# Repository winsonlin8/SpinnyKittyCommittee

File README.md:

# Spinning Cat Speaker

A rhythm-synchronized speaker system featuring a 3D-printed cat that spins and flashes RGB LEDs in time with music — inspired by [this video](https://www.youtube.com/watch?v=IxX_QHay02M).

**Group Members:** Katherine Han, Evan Ho, Hajime Kioi, Winson Lin

---

## Overview

The Spinning Cat Speaker is a custom-built embedded audio system that plays music while driving a DC motor to spin a 3D-printed cat figurine in sync with the beat. An RGB LED ring mounted on the assembly pulses with the music for a visual effect that complements the audio.

The system is powered via a 5V USB connection and streams audio and motor movement data concurrently from a microSD card. Physical buttons allow the user to cycle through tracks, control playback, and trigger LED effects.

---

## Features

- Music playback from microSD card over I2S to a Class D amplifier
- Motor speed and direction synchronized to music rhythm
- 35-LED WS2812 RGB ring with programmable lighting effects
- Microphone input for audio-reactive modes
- 8-button interface: Play/Pause, Volume Up/Down, Next, Previous, LED Trigger, Microphone Trigger, and a spare
- 5V USB powered

---

## System Architecture

The system is built around two microcontrollers:

- **ESP32** (Main Compute) — handles audio decoding and playback, microSD streaming via SPI, I2S audio output to the amplifier and input from the microphone, button input handling, and I2C communication to the peripheral controller.
- **MSPM0G3507** (Peripheral Control) — receives commands from the ESP32 over I2C and drives the motor via PWM/GPIO to the L298N motor driver, and controls the WS2812 LED ring over a 1-wire interface.

### Component Summary

| Component | Role |
|---|---|
| ESP32 | Main compute: audio, SD, buttons, I2C master |
| MSPM0G3507 | Peripheral control: motor, LEDs (I2C target) |
| ADA254 (microSD Breakout) | Music and movement file storage (SPI) |
| ICS-43434 | MEMS microphone (I2S) |
| MAX98357A | I2S Class D amplifier |
| EK1725 (2"–3", 4Ω, 3W) | Speaker |
| L298N | DC motor driver (PWM + GPIO direction) |
| DC Motor | Spins the cat |
| 35x WS2812 5050 LED Ring | RGB lighting effects (1-wire) |
| 8 Buttons | User input (GPIO with pull-ups) |

### System Diagram

---

## Power

The entire system is powered from a single **5V USB** connection.

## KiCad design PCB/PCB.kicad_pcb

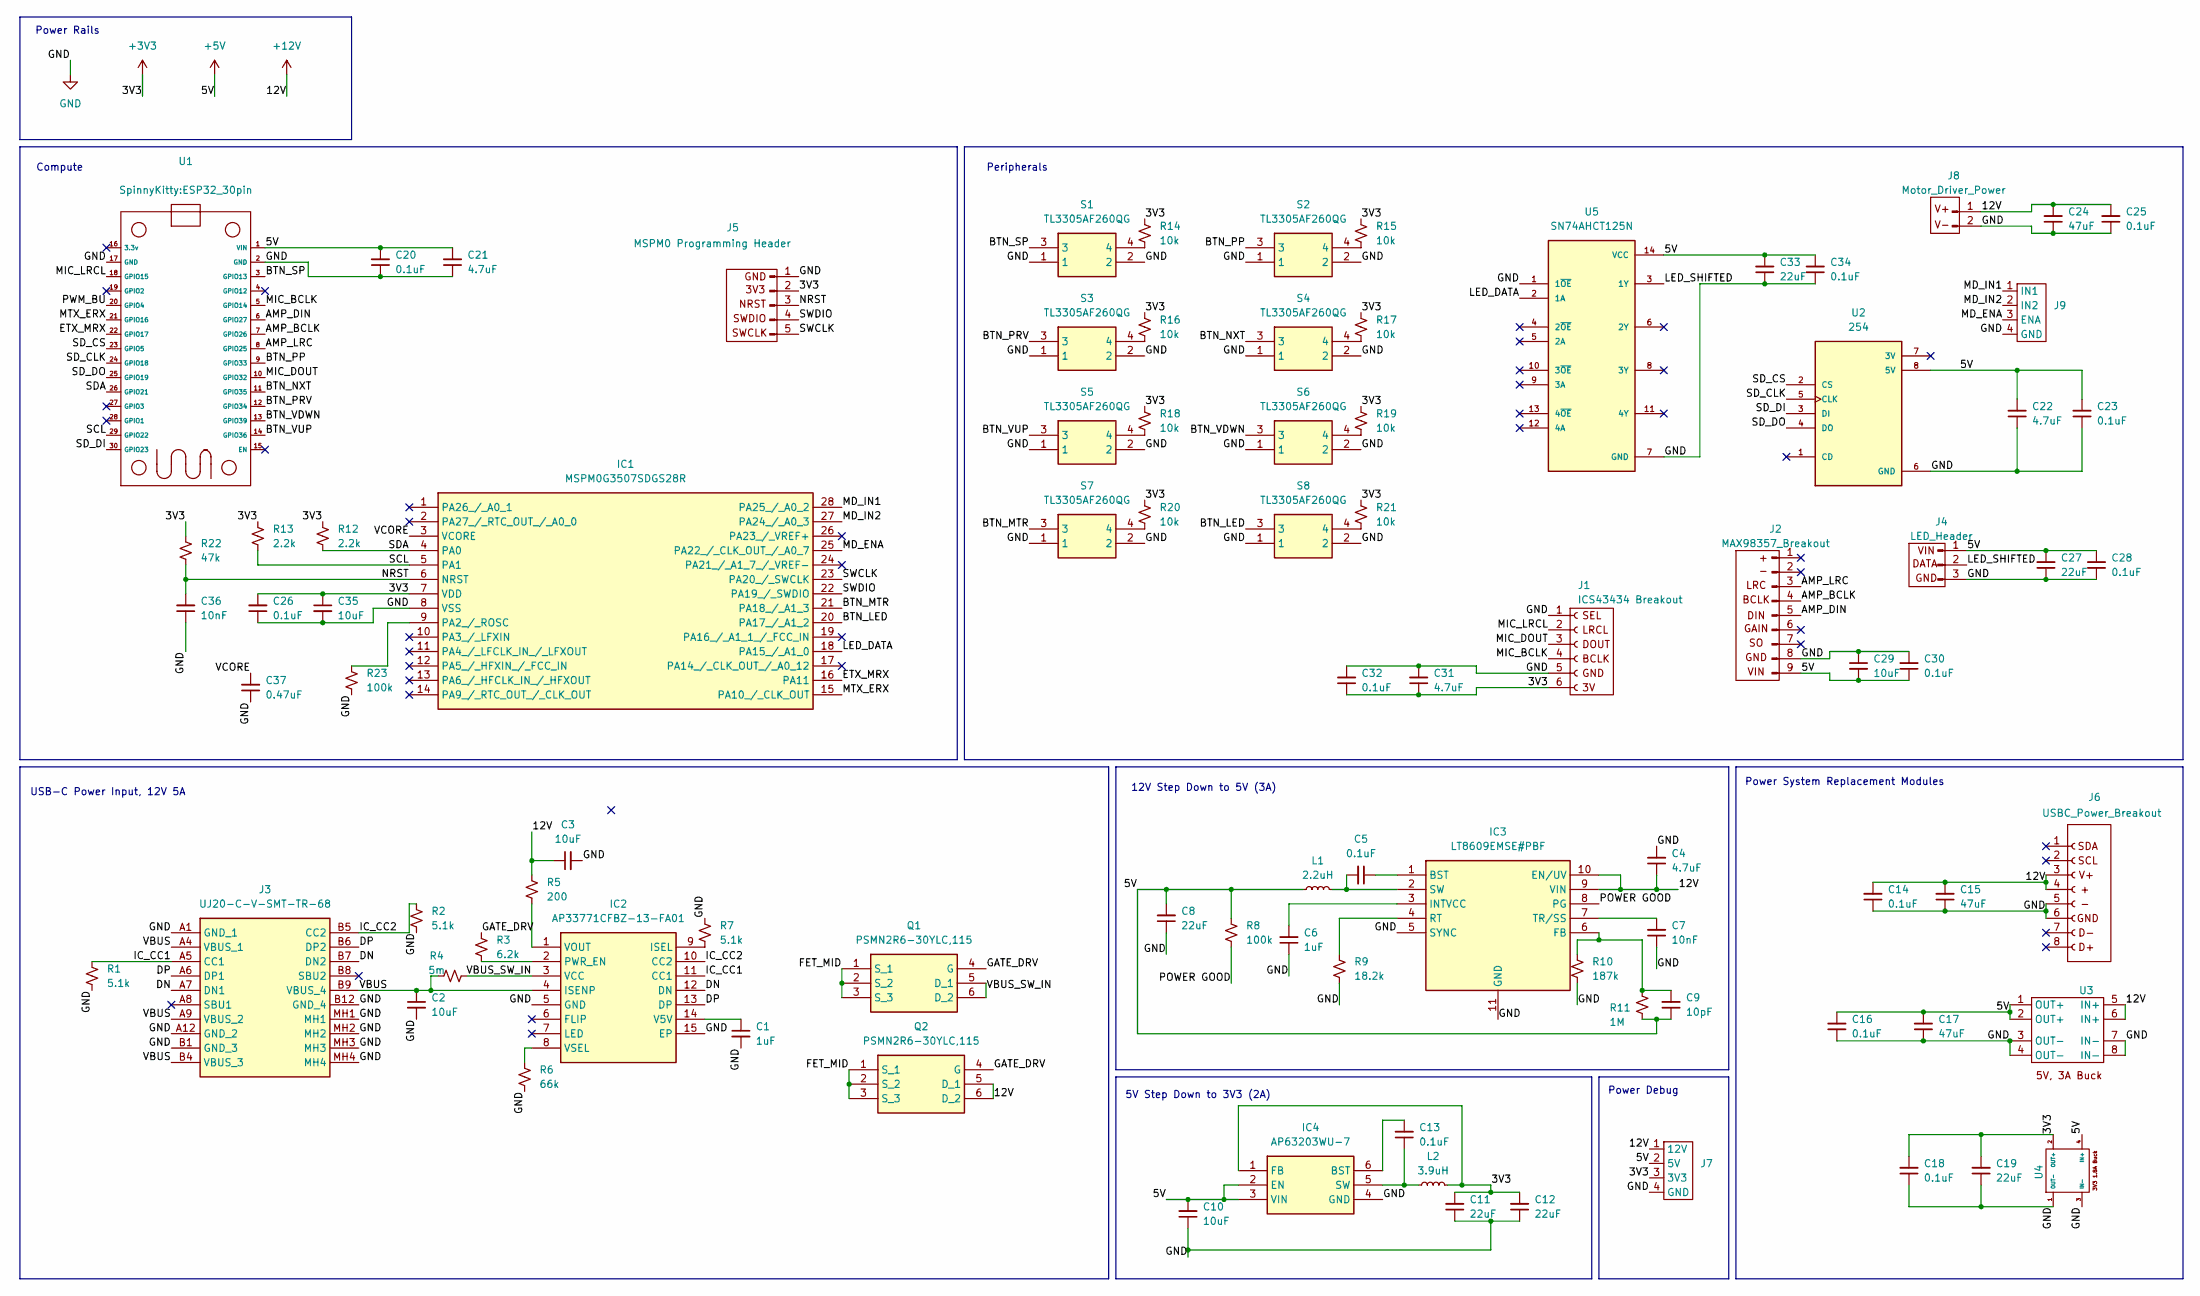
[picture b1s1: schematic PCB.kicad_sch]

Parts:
C1, C6: 1uF; C_0805_2012Metric_Pad1.18x1.45mm_HandSolder; Mouser Part Number 581-KGM21AR71E105JU
C2, C3, C10, C29, C35: 10uF; C_1206_3216Metric_Pad1.33x1.80mm_HandSolder; Mouser Part Number 963-BAST31LAB7106KT
C4, C21, C22, C31: 4.7uF; C_0805_2012Metric_Pad1.18x1.45mm_HandSolder; Mouser Part Number KGM21AR71E475KU
C5, C13, C14, C16, C18, C20, C23, C25, C26, C28, C30, C32, C34: 0.1uF; C_0805_2012Metric_Pad1.18x1.45mm_HandSolder; Mouser Part Number 581-KAM21BR71E104MT
C7, C36: 10nF; C_0805_2012Metric_Pad1.18x1.45mm_HandSolder; Mouser Part Number 581-08053C103JAZ2A
C8, C11, C12, C19, C27, C33: 22uF; C_1206_3216Metric_Pad1.33x1.80mm_HandSolder; Mouser Part Number 963-MSASE31LBB7226MT
C9: 10pF; C_0805_2012Metric_Pad1.18x1.45mm_HandSolder; Mouser Part Number 581-08053A100JAT2A
C15, C17, C24: 47uF; C_0805_2012Metric_Pad1.18x1.45mm_HandSolder; Mouser Part Number 810-C3216X5R1E476M
C37: 0.47uF; C_0805_2012Metric_Pad1.18x1.45mm_HandSolder; Mouser Part Number 581-08055C474K4T4A
IC1: MSPM0G3507SDGS28R; SOP50P490X110-28N; Mouser Part Number 595-MSPM0G3507SDG28R
IC2: AP33771CFBZ-13-FA01; AP33771CFBZ13FA01; Mouser Part Number 621-P33771CFBZ13FA01
IC3: LT8609EMSE#PBF; SOP50P490X110-11N; Mouser Part Number 584-LT8609EMSE#PBF
IC4: AP63203WU-7; AP63203WU7; Mouser Part Number 621-AP63203WU-7
J1: ICS43434 Breakout
J2: MAX98357_Breakout; MAX98357
J3: UJ20-C-V-SMT-TR-68; UJ20CVSMTTR68; Mouser Part Number 179-UJ20-C-V-SMTTR68
J4: LED_Header; PinHeader_1x03_P2.54mm_Vertical
J5: MSPM0 Programming Header; PinHeader_1x05_P2.54mm_Vertical
J6: USBC_Power_Breakout; USBC_POWER_BREAKOUT
J7, J9: PinHeader_1x04_P2.54mm_Vertical
J8: Motor_Driver_Power; PinHeader_1x02_P2.54mm_Vertical
L1: 2.2uH; PM5402222NLT; Mouser Part Number 673-PM5402.222NLT
L2: 3.9uH; SRR3818A3R9Y; Mouser Part Number 652-SRR3818A-3R9Y
Q1, Q2: PSMN2R6-30YLC,115; PSMN2R630YLC115; Mouser Part Number 771-PSMN2R630YLC115
R1, R2, R7: 5.1k; R_0603_1608Metric_Pad0.98x0.95mm_HandSolder; Mouser Part Number 71-TNPW06035K10FHTA
R3: 6.2k; R_0603_1608Metric_Pad0.98x0.95mm_HandSolder; Mouser Part Number 594-MCT06030C6201FP5
R4: 5m; R_2512_6332Metric_Pad1.40x3.35mm_HandSolder; Mouser Part Number 71-WSLP25125L000FEA
R5: 200; R_0603_1608Metric_Pad0.98x0.95mm_HandSolder; Mouser Part Number 594-MCT06030C2000FP5
R6: 66k; R_0603_1608Metric_Pad0.98x0.95mm_HandSolder; Mouser Part Number 279-CPF0603F66K5C1
R8: 100k; R_0603_1608Metric_Pad0.98x0.95mm_HandSolder; Mouser Part Number 594-MCT06030C1003FP5
R9: 18.2k; R_0603_1608Metric_Pad0.98x0.95mm_HandSolder; Mouser Part Number 594-MCT06030C1822FP5
R10: 187k; R_0603_1608Metric_Pad0.98x0.95mm_HandSolder; Mouser Part Number 603-RT0603FRE07187KL
R11: 1M; R_0603_1608Metric_Pad0.98x0.95mm_HandSolder; Mouser Part Number 660-RK73G1JRTTD1004F
R12, R13: 2.2k; R_0603_1608Metric_Pad0.98x0.95mm_HandSolder; Mouser Part Number 594-MCT06030C2201FP5
R14, R15, R16, R17, R18, R19, R20, R21: 10k; R_0603_1608Metric_Pad0.98x0.95mm_HandSolder; Mouser Part Number 71-TNPW060310K0FEEA
R22: 47k; R_0603_1608Metric_Pad0.98x0.95mm_HandSolder; Mouser Part Number 594-MCT06030C4702FP5
R23: 100k; R_0805_2012Metric_Pad1.20x1.40mm_HandSolder; Mouser Part Number 708-RNCF0805TKT100K
S1, S2, S3, S4, S5, S6, S7, S8: TL3305AF260QG; TL3305AF160QG; Mouser Part Number 612-TL3305AF260QG
U1: ESP32_30pin
U2: 254; MODULE_254; PARTREV Jul 31, 2013
U3: 5V 3A Buck
U4: 3V3 1.8A Buck
U5: SN74AHCT125N; DIP794W45P254L1930H508Q14; PARTREV Q

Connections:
+3V3: C11.2, C12.2, C18.2, C19.2, C26.2, C31.1, C32.1, C35.1, IC1.7 (VDD), IC4.1 (FB), J1.6 (3V), J5.2 (3V3), J7.3 (3V3), L2.2, R12.1, R13.1, R14.1, R15.1, R16.1, R17.1, R18.1, R19.1, R20.1, R21.1, R22.1, U4.2 (OUT+)
+5V: C8.2, C9.1, C10.2, C16.2, C17.2, C20.2, C21.2, C22.2, C23.2, C27.2, C28.2, C29.2, C30.1, C33.2, C34.2, IC4.2 (EN), IC4.3 (VIN), J2.9 (VIN), J4.1 (VIN), J7.2 (5V), L1.1, R8.1, R11.2, U1.1 (VIN), U2.8 (5V), U3.1 (OUT+), U3.2 (OUT+), U4.4 (IN+), U5.14 (VCC)
+12V: C3.1, C4.1, C14.2, C15.2, C24.2, C25.2, IC3.9 (VIN), IC3.10 (EN/UV), J6.3 (V+), J6.4 (+), J7.1 (12V), J8.1 (V+), Q2.5 (D_1), Q2.6 (D_2), R5.1, U3.5 (IN+), U3.6 (IN+)
/AMP_BCLK: J2.4 (BCLK), U1.7 (GPIO26)
/AMP_DIN: J2.5 (DIN), U1.6 (GPIO27)
/AMP_LRC: J2.3 (LRC), U1.8 (GPIO25)
/BTN_LED: IC1.20 (PA17_/_A1_2), S8.3
/BTN_MTR: IC1.21 (PA18_/_A1_3), S7.3
/BTN_NXT: S4.3, U1.11 (GPIO35)
/BTN_PP: S2.3, U1.9 (GPIO33)
/BTN_PRV: S3.3, U1.12 (GPIO34)
/BTN_SP: S1.3, U1.3 (GPIO13)
/BTN_VDWN: S6.3, U1.13 (GPIO39)
/BTN_VUP: S5.3, U1.14 (GPIO36)
/DN: IC2.12 (DN), J3.A7 (DN1), J3.B7 (DN2)
/DP: IC2.13 (DP), J3.A6 (DP1), J3.B6 (DP2)
/ETX_MRX: IC1.16 (PA11), U1.22 (GPIO17)
/FET_MID: Q1.1 (S_1), Q1.2 (S_2), Q1.3 (S_3), Q2.1 (S_1), Q2.2 (S_2), Q2.3 (S_3)
/GATE_DRV: Q1.4 (G), Q2.4 (G), R3.1
/IC_CC1: IC2.11 (CC1), J3.A5 (CC1), R1.1
/IC_CC2: IC2.10 (CC2), J3.B5 (CC2), R2.1
/LED_DATA: IC1.18 (PA15_/_A1_0), U5.2 (1A)
/LED_SHIFTED: J4.2 (DATA), U5.3 (1Y)
/MD_ENA: IC1.25 (PA22_/_CLK_OUT_/_A0_7), J9.3 (ENA)
/MD_IN1: IC1.28 (PA25_/_A0_2), J9.1 (IN1)
/MD_IN2: IC1.27 (PA24_/_A0_3), J9.2 (IN2)
/MIC_BCLK: J1.4 (BCLK), U1.5 (GPIO14)
/MIC_DOUT: J1.3 (DOUT), U1.10 (GPIO32)
/MIC_LRCL: J1.2 (LRCL), U1.18 (GPIO15)
/MTX_ERX: IC1.15 (PA10_/_CLK_OUT), U1.21 (GPIO16)
/NRST: C36.2, IC1.6 (NRST), J5.3 (NRST), R22.2
/POWER GOOD: IC3.8 (PG), R8.2
/PWM_BU: U1.20 (GPIO4)
/SCL: IC1.5 (PA1), R13.2, U1.29 (GPIO22)
/SDA: IC1.4 (PA0), R12.2, U1.26 (GPIO21)
/SD_CLK: U1.24 (GPIO18), U2.5 (CLK)
/SD_CS: U1.23 (GPIO5), U2.2 (CS)
/SD_DI: U1.30 (GPIO23), U2.3 (DI)
/SD_DO: U1.25 (GPIO19), U2.4 (DO)
/SWCLK: IC1.23 (PA20_/_SWCLK), J5.5 (SWCLK)
/SWDIO: IC1.22 (PA19_/_SWDIO), J5.4 (SWDIO)
/VBUS: C2.1, IC2.4 (ISENP), J3.A4 (VBUS_1), J3.A9 (VBUS_2), J3.B4 (VBUS_3), J3.B9 (VBUS_4), R4.1
/VBUS_SW_IN: IC2.3 (VCC), Q1.5 (D_1), Q1.6 (D_2), R4.2
/VCORE: C37.2, IC1.3 (VCORE)
GND: C1.2, C2.2, C3.2, C4.2, C6.1, C7.1, C8.1, C10.1, C11.1, C12.1, C14.1, C15.1, C16.1, C17.1, C18.1, C19.1, C20.1, C21.1, C22.1, C23.1, C24.1, C25.1, C26.1, C27.1, C28.1, C29.1, C30.2, C31.2, C32.2, C33.1, C34.1, C35.2, C36.1, C37.1, IC1.8 (VSS), IC2.5 (GND), IC2.15 (EP), IC3.5 (SYNC), IC3.11 (GND), IC4.4 (GND), J1.1 (SEL), J1.5 (GND), J2.8 (GND), J3.A1 (GND_1), J3.A12 (GND_2), J3.B1 (GND_3), J3.B12 (GND_4), J3.MH1, J3.MH2, J3.MH3, J3.MH4, J4.3 (GND), J5.1 (GND), J6.5 (-), J6.6 (GND), J7.4 (GND), J8.2 (V-), J9.4 (GND), R1.2, R2.2, R6.2, R7.1, R9.2, R10.2, R23.2, S1.1, S1.2, S2.1, S2.2, S3.1, S3.2, S4.1, S4.2, S5.1, S5.2, S6.1, S6.2, S7.1, S7.2, S8.1, S8.2, U1.2 (GND), U1.17 (GND), U2.6 (GND), U3.3 (OUT-), U3.4 (OUT-), U3.7 (IN-), U3.8 (IN-), U4.1 (OUT-), U4.3 (IN-), U5.1 (1~OE), U5.7 (GND)
unnamed: IC1.9 (PA2_/_ROSC), R23.1
unnamed: IC2.9 (ISEL), R7.2
unnamed: IC2.2 (PWR_EN), R3.2
unnamed: C1.1, IC2.14 (V5V)
unnamed: IC2.1 (VOUT), R5.2
unnamed: IC2.8 (VSEL), R6.1
unnamed: C5.1, IC3.1 (BST)
unnamed: C9.2, IC3.6 (FB), R10.1, R11.1
unnamed: C6.2, IC3.3 (INTVCC)
unnamed: IC3.4 (RT), R9.1
unnamed: C5.2, IC3.2 (SW), L1.2
unnamed: C7.2, IC3.7 (TR/SS)
unnamed: C13.2, IC4.6 (BST)
unnamed: C13.1, IC4.5 (SW), L2.1
unnamed: R14.2, S1.4
unnamed: R15.2, S2.4
unnamed: R16.2, S3.4
unnamed: R17.2, S4.4
unnamed: R18.2, S5.4
unnamed: R19.2, S6.4
unnamed: R20.2, S7.4
unnamed: R21.2, S8.4

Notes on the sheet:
5V Step Down to 3V3 (2A)
Peripherals
Power Debug
Compute
USB-C Power Input, 12V 5A
Power Rails
Power System Replacement Modules
12V Step Down to 5V (3A)

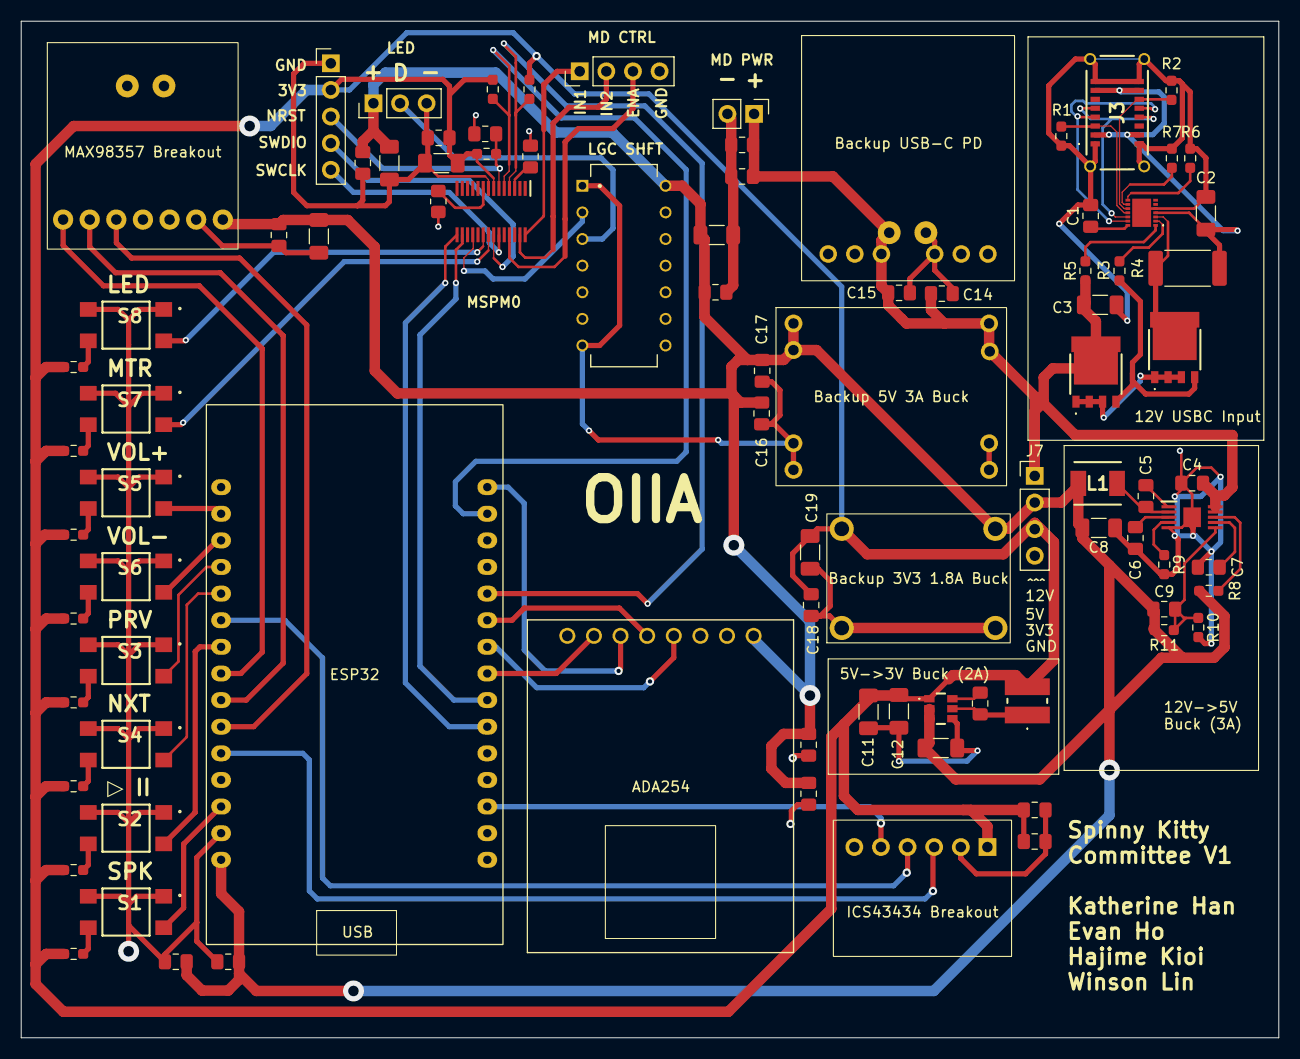
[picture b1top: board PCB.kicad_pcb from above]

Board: 2 copper layers, 120.0 x 97.0 mm, 90 parts (0 on the bottom side), 66 nets.

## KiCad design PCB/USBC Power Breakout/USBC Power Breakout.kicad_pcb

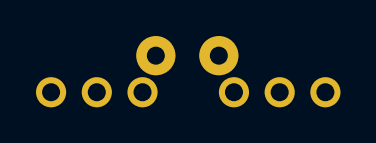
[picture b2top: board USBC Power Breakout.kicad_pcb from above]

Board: 2 copper layers, 4 parts (1 on the bottom side), 2 nets.

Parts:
JP3, JP4: 1X03_ROUND
PLABEL3: PLABEL3
X4: 3.5mm; TERMBLOCK_1X2-3.5MM

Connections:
GND: JP4.1, X4.2
VOUT: JP3.1, X4.1

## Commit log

2026-04-04 Add microsd PlatformIO project
2026-04-04 Rename project from 'elec327project' to 'Spinning Cat Speaker'
2026-04-04 rename microsd ESP32
2026-04-04 added platformio readme
2026-04-04 added wiring to README
2026-04-04 added kicad pcb files
2026-04-04 update project description
2026-04-04 fix broken link
2026-04-04 setup future commit locations
2026-04-08 Update README.md for speaker
2026-04-08 pcb update
2026-04-08 all symbols and footprints
2026-04-09 Update README.md for mic
2026-04-10 Add files via upload
    Files for running PWM. The motor should change speed every 2s.
2026-04-10 Update README.md
    Pin documentation for running PWM
2026-04-10 Update README.md for esp32 to mspm0
2026-04-10 Update README.md
    pinout for PWM
2026-04-10 Update main.c
    PWM code
    changes between fast and slow rotation every 2s
2026-04-11 schematic for on board power system
2026-04-11 backup power rail pcb
2026-04-11 schematic update
2026-04-11 drc update
2026-04-12 Update README.md I2C
2026-04-13 complete pcb
2026-04-13 routing cleanup
2026-04-13 mspm0 update
2026-05-03 final mspm0 ccs project
2026-05-03 Create final.ccs
    Final ESP32 Code
2026-05-03 Final ESP32 Code
2026-05-05 pcb backups
2026-05-05 cleanup and comments
